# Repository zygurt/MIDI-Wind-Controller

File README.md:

# MIDI-Wind-Controller

## A brief overview of the repo

- 3D designs contains dxf and svg files.  Basic design was done in Fusion 360 and then exported.
- Datasheets contains datasheets. Woah.
- src contains source code for doppler and Arduino Leonardo implementations, as well as the board schematic.  Currently midi messages are sent over USB, and shows the midi note number in binary on the LED grid on the doppler board.

## Known issues
- Pressing the low C key (D9) causes the doppler to crash.  Reducing the length of the readButtons() switch case to 7 statements stops the crashing.  The error isn't present on the Arduino Leonardo.
- The octave keys give incorrect values for C#. Top 2 octaves are swapped. Again, this error does not occur for the Arduino Leonardo.

Updates are occasionally posted on [Instagram](https://www.instagram.com/zygurt/)

## Current prototype status:

## Legacy information
Videos about the initial prototype can be found on [Youtube](https://www.youtube.com/watch?v=xT4aQg9pAro&list=PLZOH4oUjroN9ol0y3P3p1gkSgcQwLBbCZ)

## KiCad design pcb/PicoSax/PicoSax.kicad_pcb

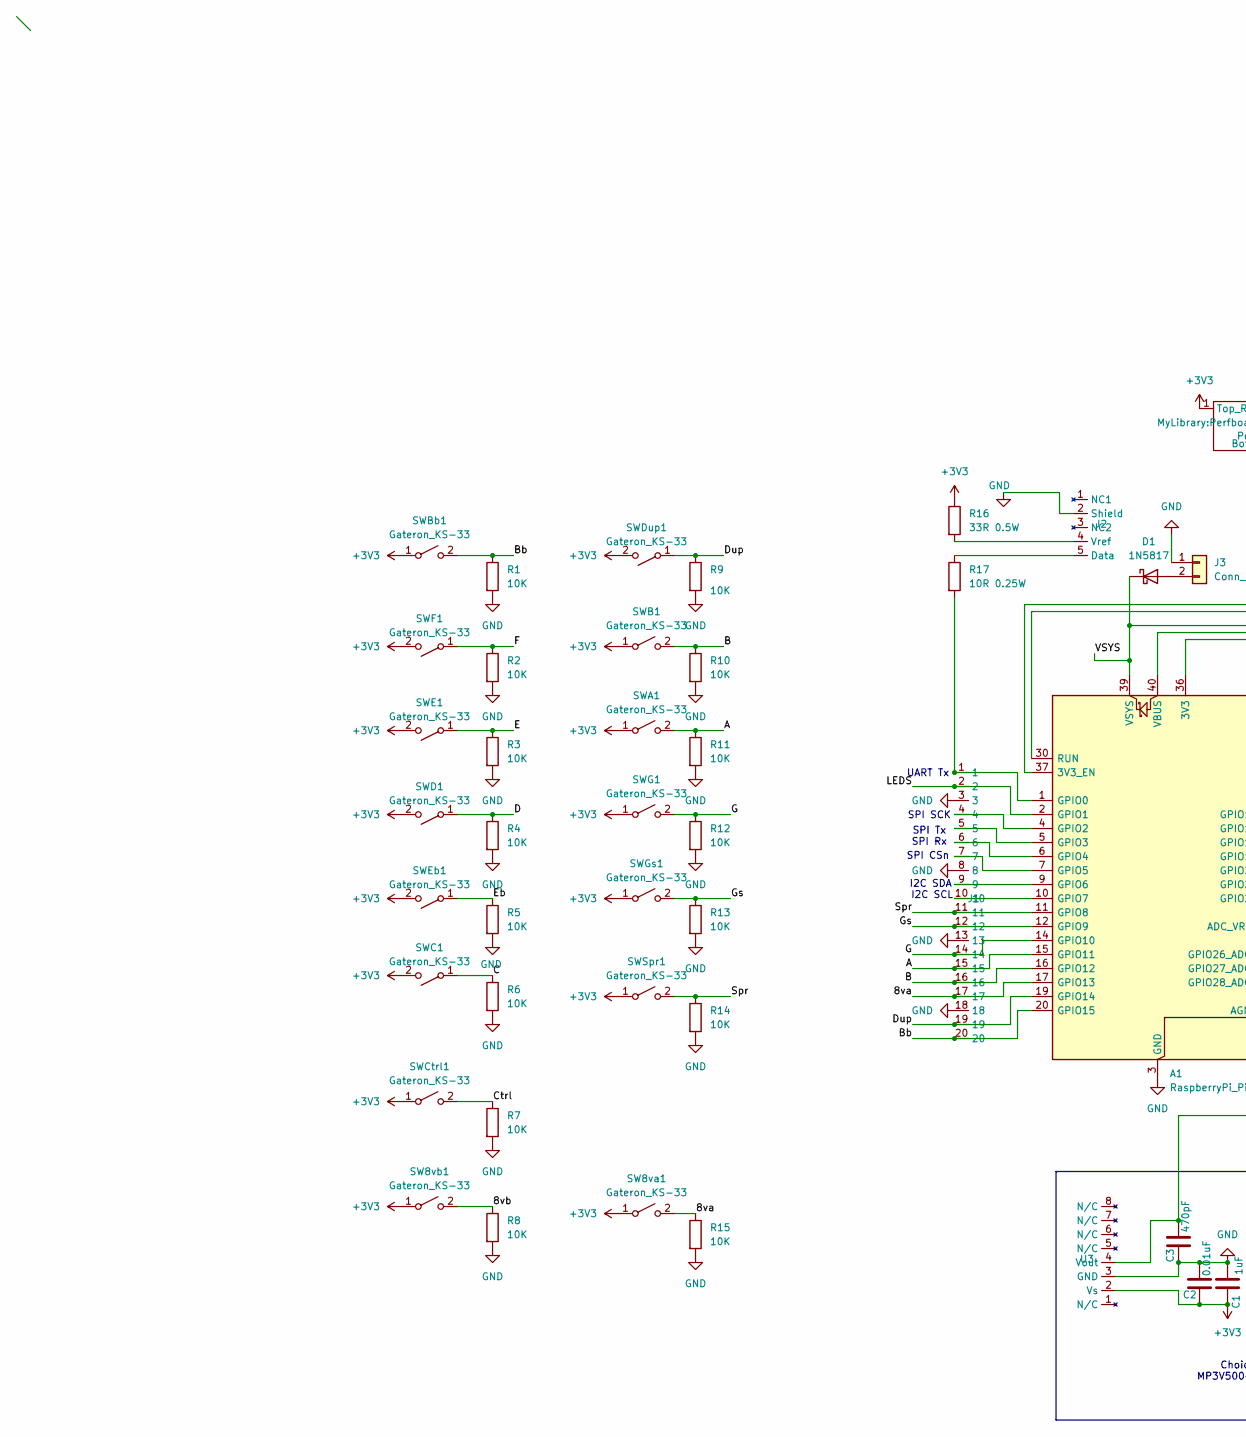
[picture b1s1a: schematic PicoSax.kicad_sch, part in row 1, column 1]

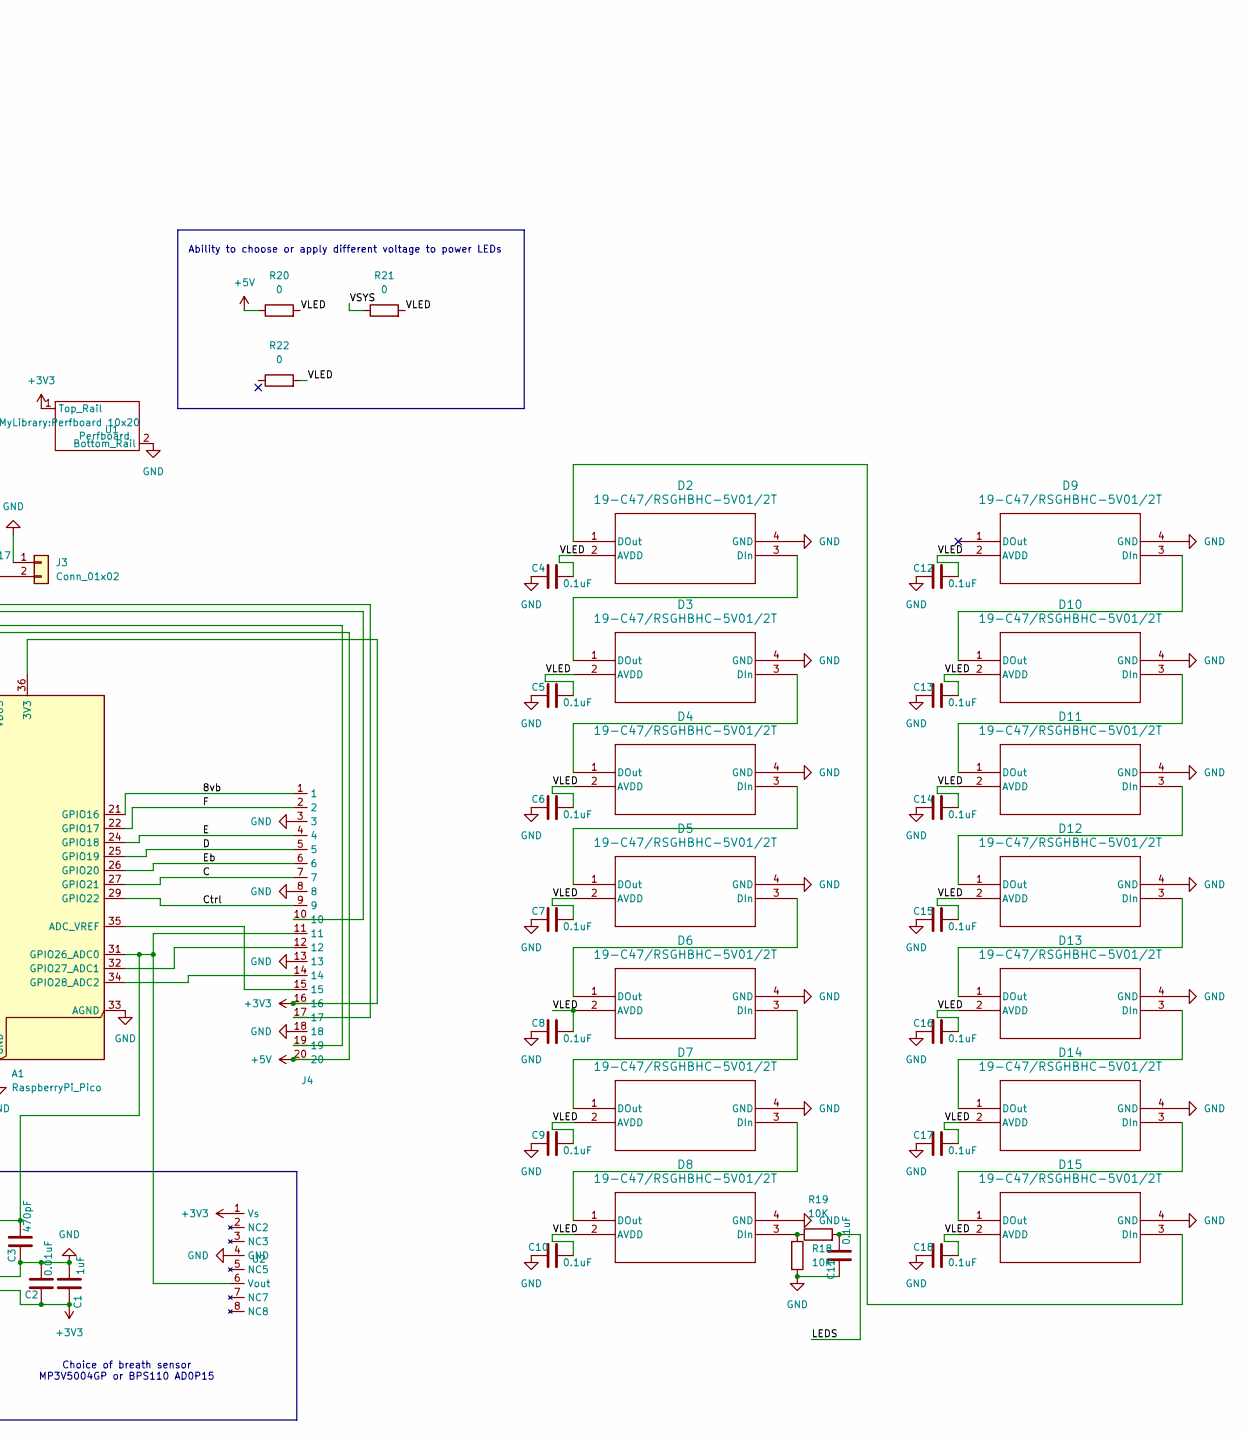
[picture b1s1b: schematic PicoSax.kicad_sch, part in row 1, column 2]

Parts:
A1: RaspberryPi_Pico; RaspberryPi_Pico_Common_Unspecified
C1: 1uF; C_0805_2012Metric_Pad1.18x1.45mm_HandSolder
C2: 0.01uF; C_0805_2012Metric_Pad1.18x1.45mm_HandSolder
C3: 470pF; C_0805_2012Metric_Pad1.18x1.45mm_HandSolder
C4, C5, C6, C7, C8, C9, C10, C11, C12, C13, C14, C15, C16, C17, C18: 0.1uF; C_0805_2012Metric_Pad1.18x1.45mm_HandSolder
D1: 1N5817; D_DO-41_SOD81_P10.16mm_Horizontal
D2, D3, D4, D5, D6, D7, D8, D9, D10, D11, D12, D13, D14, D15: 19-C47/RSGHBHC-5V01/2T; 19-C47_RSGHBHC-5V01-2T
J1, J4: PiPico Header
J2: MIDI_DIN5
J3: Conn_01x02; PinHeader_1x02_P2.54mm_Vertical
R1, R2, R3, R4, R5, R6, R7, R8, R9, R10, R11, R12, R13, R14, R15, R18, R19: 10K; R_0805_2012Metric_Pad1.20x1.40mm_HandSolder
R16: 33R 0.5W; R_1210_3225Metric_Pad1.30x2.65mm_HandSolder
R17: 10R 0.25W; R_0805_2012Metric_Pad1.20x1.40mm_HandSolder
R20, R21, R22: 0; R_0805_2012Metric_Pad1.20x1.40mm_HandSolder
SW8va1, SW8vb1: Gateron_KS-33; KS-33
SWA1: Gateron_KS-33; KS-33
SWB1: Gateron_KS-33; KS-33
SWBb1: Gateron_KS-33; KS-33
SWC1: Gateron_KS-33; KS-33
SWCtrl1: Gateron_KS-33; KS-33
SWD1: Gateron_KS-33; KS-33
SWDup1: Gateron_KS-33; KS-33
SWE1: Gateron_KS-33; KS-33
SWEb1: Gateron_KS-33; KS-33
SWF1: Gateron_KS-33; KS-33
SWG1: Gateron_KS-33; KS-33
SWGs1: Gateron_KS-33; KS-33
SWSpr1: Gateron_KS-33; KS-33
U1: Perfboard; Perfboard 10x20
U2: BPS110 AD0P15
U3: MP3V5004GP

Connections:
+3V3: A1.36 (3V3), C1.2, C2.2, J4.16, R16.1, SW8va1.1 (A), SW8vb1.1 (A), SWA1.1 (A), SWB1.1 (A), SWBb1.1 (A), SWC1.2 (B), SWCtrl1.1 (A), SWD1.2 (B), SWDup1.2 (B), SWE1.2 (B), SWEb1.2 (B), SWF1.2 (B), SWG1.1 (A), SWGs1.1 (A), SWSpr1.1 (A), U1.1 (Top_Rail), U2.1 (Vs), U3.2 (Vs)
+5V: A1.40 (VBUS), J4.20, R20.1
/8va: A1.17 (GPIO13), J1.17, R15.1, SW8va1.2 (B)
/8vb: A1.21 (GPIO16), J4.1, R8.1, SW8vb1.2 (B)
/A: A1.15 (GPIO11), J1.15, R11.1, SWA1.2 (B)
/B: A1.16 (GPIO12), J1.16, R10.1, SWB1.2 (B)
/Bb: A1.20 (GPIO15), J1.20, R1.1, SWBb1.2 (B)
/C: A1.27 (GPIO21), J4.7, R6.1, SWC1.1 (A)
/Ctrl: A1.29 (GPIO22), J4.9, R7.1, SWCtrl1.2 (B)
/D: A1.25 (GPIO19), J4.5, R4.1, SWD1.1 (A)
/Dup: A1.19 (GPIO14), J1.19, R9.1, SWDup1.1 (A)
/E: A1.24 (GPIO18), J4.4, R3.1, SWE1.1 (A)
/Eb: A1.26 (GPIO20), J4.6, R5.1, SWEb1.1 (A)
/F: A1.22 (GPIO17), J4.2, R2.1, SWF1.1 (A)
/G: A1.14 (GPIO10), J1.14, R12.1, SWG1.2 (B)
/Gs: A1.12 (GPIO9), J1.12, R13.1, SWGs1.2 (B)
/LEDS: A1.2 (GPIO1), C11.1, J1.2, R19.2
/Spr: A1.11 (GPIO8), J1.11, R14.1, SWSpr1.2 (B)
/VLED: C4.1, C5.1, C6.1, C7.1, C8.1, C9.1, C10.1, C12.1, C13.1, C14.1, C15.1, C16.1, C17.1, C18.1, D2.2 (AVDD), D3.2 (AVDD), D4.2 (AVDD), D5.2 (AVDD), D6.2 (AVDD), D7.2 (AVDD), D8.2 (AVDD), D9.2 (AVDD), D10.2 (AVDD), D11.2 (AVDD), D12.2 (AVDD), D13.2 (AVDD), D14.2 (AVDD), D15.2 (AVDD), R20.2, R21.2, R22.2
/VSYS: A1.39 (VSYS), D1.1 (K), J4.19, R21.1
GND: A1.3 (GND), A1.8 (GND), A1.13 (GND), A1.18 (GND), A1.23 (GND), A1.28 (GND), A1.33 (AGND), A1.38 (GND), C1.1, C2.1, C3.2, C4.2, C5.2, C6.2, C7.2, C8.2, C9.2, C10.2, C11.2, C12.2, C13.2, C14.2, C15.2, C16.2, C17.2, C18.2, D2.4 (GND), D3.4 (GND), D4.4 (GND), D5.4 (GND), D6.4 (GND), D7.4 (GND), D8.4 (GND), D9.4 (GND), D10.4 (GND), D11.4 (GND), D12.4 (GND), D13.4 (GND), D14.4 (GND), D15.4 (GND), J1.3, J1.8, J1.13, J1.18, J2.2 (Shield), J3.1, J4.3, J4.8, J4.13, J4.18, R1.2, R2.2, R3.2, R4.2, R5.2, R6.2, R7.2, R8.2, R9.2, R10.2, R11.2, R12.2, R13.2, R14.2, R15.2, R18.2, U1.2 (Bottom_Rail), U2.4 (GND), U3.3 (GND)
unnamed: A1.37 (3V3_EN), J4.17
unnamed: A1.35 (ADC_VREF), J4.15
unnamed: A1.1 (GPIO0), J1.1, R17.2
unnamed: A1.4 (GPIO2), J1.4
unnamed: A1.5 (GPIO3), J1.5
unnamed: A1.6 (GPIO4), J1.6
unnamed: A1.7 (GPIO5), J1.7
unnamed: A1.9 (GPIO6), J1.9
unnamed: A1.10 (GPIO7), J1.10
unnamed: A1.31 (GPIO26_ADC0), C3.1, J4.11, U2.6 (Vout), U3.4 (Vout)
unnamed: A1.32 (GPIO27_ADC1), J4.12
unnamed: A1.34 (GPIO28_ADC2), J4.14
unnamed: A1.30 (RUN), J4.10
unnamed: D1.2 (A), J3.2
unnamed: D2.3 (DIn), D3.1 (DOut)
unnamed: D3.3 (DIn), D4.1 (DOut)
unnamed: D4.3 (DIn), D5.1 (DOut)
unnamed: D5.3 (DIn), D6.1 (DOut)
unnamed: D6.3 (DIn), D7.1 (DOut)
unnamed: D7.3 (DIn), D8.1 (DOut)
unnamed: D8.3 (DIn), R18.1, R19.1
unnamed: D10.3 (DIn), D11.1 (DOut)
unnamed: D9.3 (DIn), D10.1 (DOut)
unnamed: D11.3 (DIn), D12.1 (DOut)
unnamed: D12.3 (DIn), D13.1 (DOut)
unnamed: D13.3 (DIn), D14.1 (DOut)
unnamed: D14.3 (DIn), D15.1 (DOut)
unnamed: D2.1 (DOut), D15.3 (DIn)
unnamed: J2.5 (Data), R17.1
unnamed: J2.4 (Vref), R16.2

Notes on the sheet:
I2C SCL
SPI SCK
SPI Rx
UART Tx
SPI Tx
Ability to choose or apply different voltage to power LEDs
Choice of breath sensor MP3V5004GP or BPS110 AD0P15
SPI CSn
I2C SDA

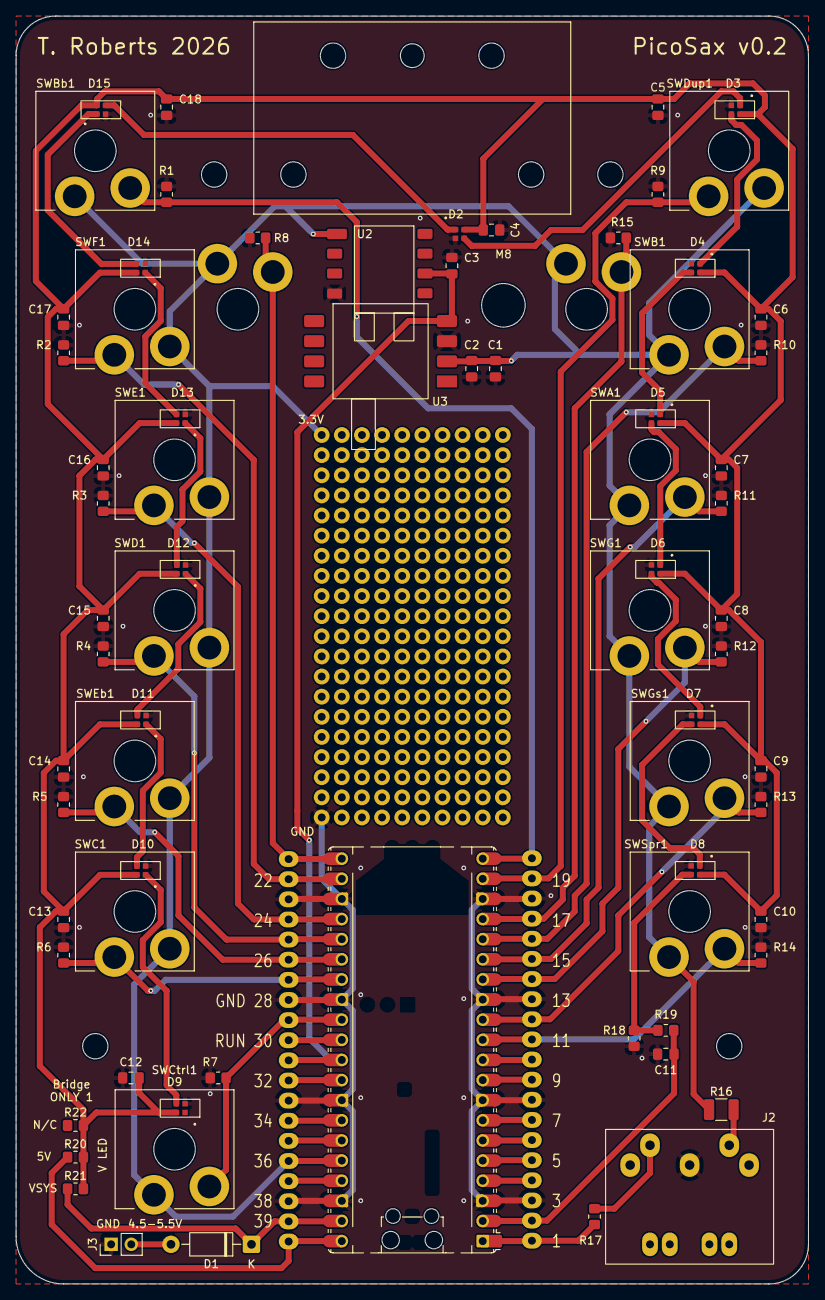
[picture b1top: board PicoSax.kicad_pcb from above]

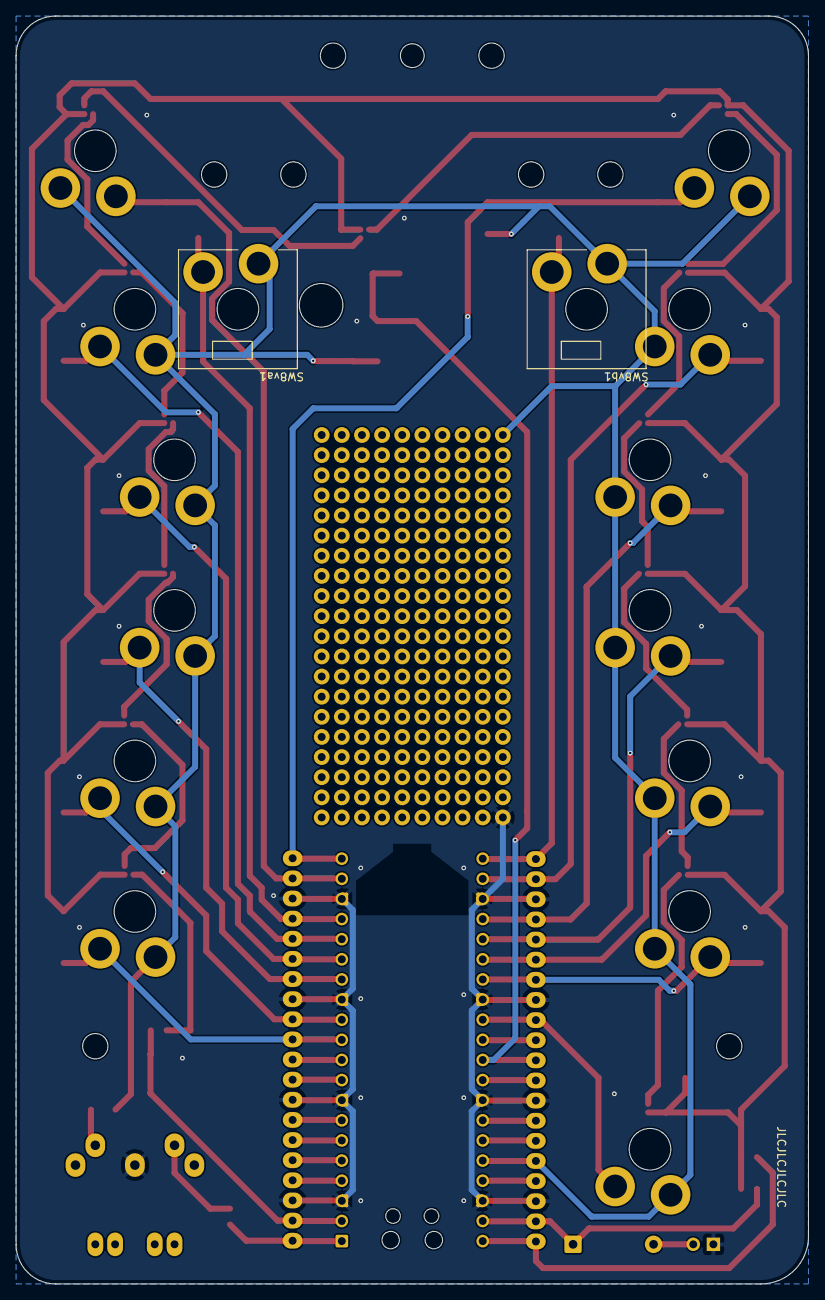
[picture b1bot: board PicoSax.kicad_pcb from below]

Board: 2 copper layers, 100.0 x 160.0 mm, 88 parts (2 on the bottom side), 51 nets.

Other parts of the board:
M1, M2, M3, M4, M5, M5#2, M6, M6#2: MountingHole_3.2mm_M3
M7: MountingHole_3mm
M8: MountingHole_5.5mm

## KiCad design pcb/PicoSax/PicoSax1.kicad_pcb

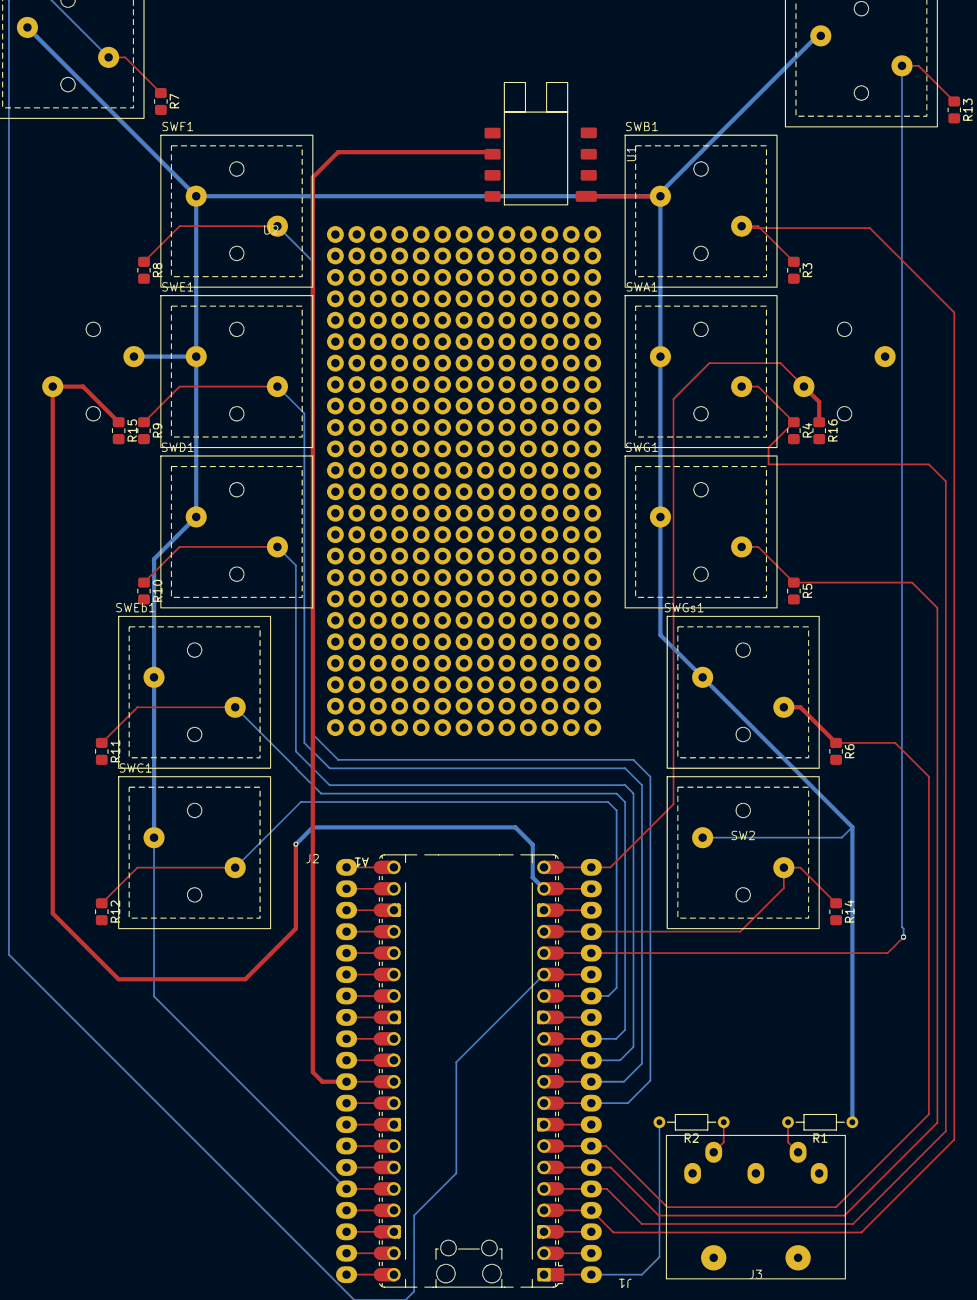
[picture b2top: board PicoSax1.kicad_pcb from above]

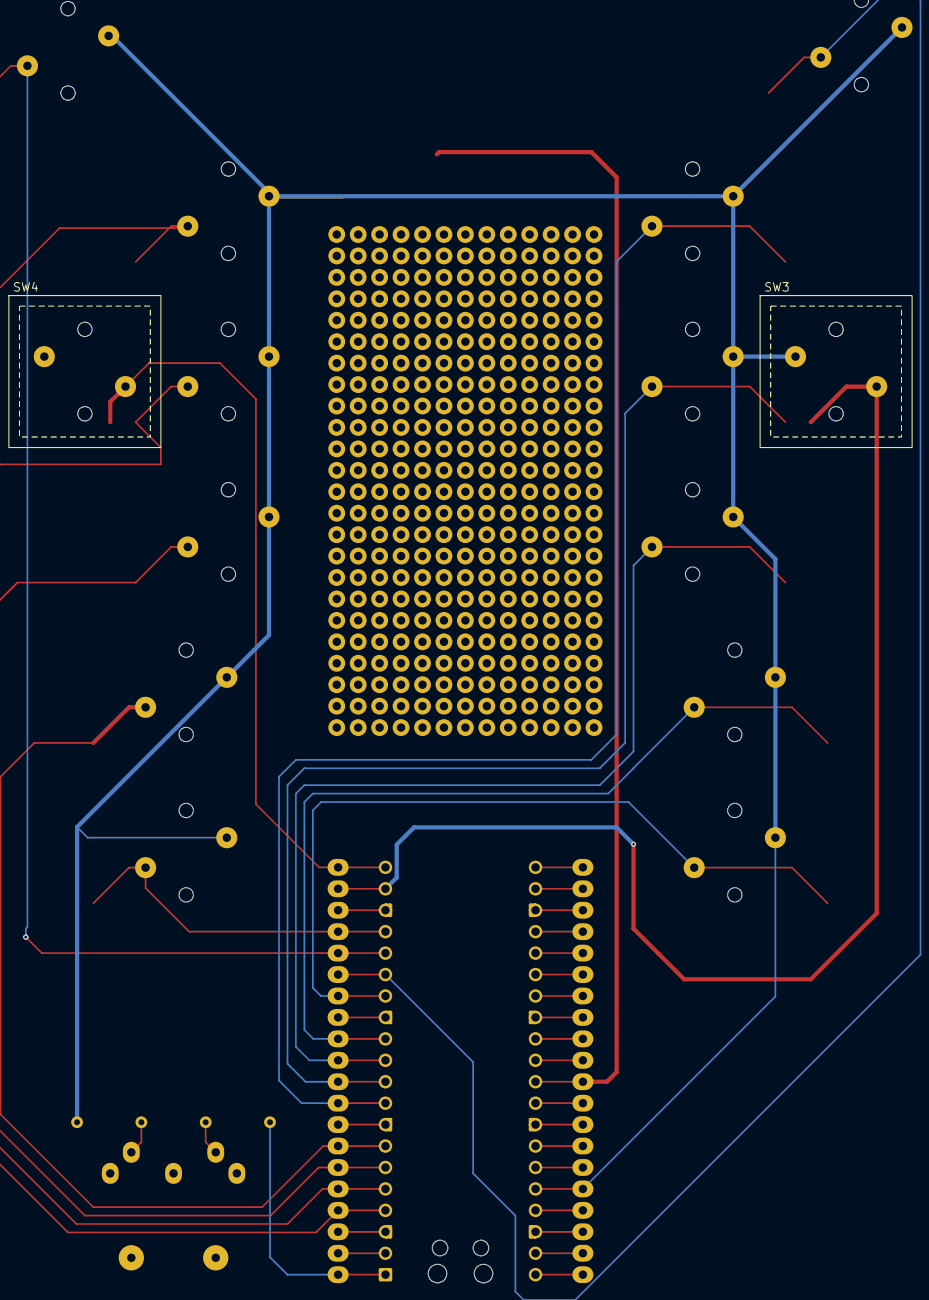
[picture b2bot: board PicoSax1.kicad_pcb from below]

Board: 2 copper layers, 36 parts (2 on the bottom side), 34 nets.

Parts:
A1: RaspberryPi_Pico; RaspberryPi_Pico_Common_Unspecified
J1, J2: PiPico Header
J3: MIDI_DIN5
R1: 33R 0.5W; R_Axial_DIN0204_L3.6mm_D1.6mm_P7.62mm_Horizontal
R2: 10R 0.25W; R_Axial_DIN0204_L3.6mm_D1.6mm_P7.62mm_Horizontal
R3, R4, R5, R6, R7, R8, R9, R10, R11, R12, R13, R14, R15, R16: 10K; R_0805_2012Metric_Pad1.20x1.40mm_HandSolder
SW1, SW2, SW3, SW4: Omron_B3K_L13L; Omron B3K L13L
SWA1: Omron_B3K_L13L; Omron B3K L13L
SWB1: Omron_B3K_L13L; Omron B3K L13L
SWBb1: Omron_B3K_L13L; Omron B3K L13L
SWC1: Omron_B3K_L13L; Omron B3K L13L
SWD1: Omron_B3K_L13L; Omron B3K L13L
SWE1: Omron_B3K_L13L; Omron B3K L13L
SWEb1: Omron_B3K_L13L; Omron B3K L13L
SWF1: Omron_B3K_L13L; Omron B3K L13L
SWG1: Omron_B3K_L13L; Omron B3K L13L
SWGs1: Omron_B3K_L13L; Omron B3K L13L
U1: BPS110 AD0P15
U2: Perfboard 13x24

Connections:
+3V3: A1.36 (3V3), J2.16, R1.1, SW1.1 (A), SW2.1 (A), SW3.1 (A), SW4.1 (A), SWA1.1 (A), SWB1.1 (A), SWBb1.1 (A), SWC1.1 (A), SWD1.1 (A), SWE1.1 (A), SWEb1.1 (A), SWF1.1 (A), SWG1.1 (A), SWGs1.1 (A), U1.1 (Vs)
GND: A1.3 (GND), A1.8 (GND), A1.13 (GND), A1.18 (GND), A1.23 (GND), A1.28 (GND), A1.33 (AGND), A1.38 (GND), J1.3, J1.8, J1.13, J1.18, J2.3, J2.8, J2.13, J2.18, J3.2 (Shield), R3.2, R4.2, R5.2, R6.2, R7.2, R8.2, R9.2, R10.2, R11.2, R12.2, R13.2, R14.2, R15.2, R16.2, U1.4 (GND)
unnamed: A1.37 (3V3_EN), J2.17
unnamed: A1.35 (ADC_VREF), J2.15
unnamed: A1.1 (GPIO0), J1.1, R2.2
unnamed: A1.4 (GPIO2), J1.4, R3.1, SWB1.2 (B)
unnamed: A1.5 (GPIO3), J1.5, R4.1, SWA1.2 (B)
unnamed: A1.6 (GPIO4), J1.6, R5.1, SWG1.2 (B)
unnamed: A1.7 (GPIO5), J1.7, R6.1, SWGs1.2 (B)
unnamed: A1.9 (GPIO6), J1.9, R8.1, SWF1.2 (B)
unnamed: A1.10 (GPIO7), J1.10, R9.1, SWE1.2 (B)
unnamed: A1.11 (GPIO8), J1.11, R10.1, SWD1.2 (B)
unnamed: A1.12 (GPIO9), J1.12, R11.1, SWEb1.2 (B)
unnamed: A1.14 (GPIO10), J1.14, R12.1, SWC1.2 (B)
unnamed: A1.15 (GPIO11), J1.15, R7.1, SWBb1.2 (B)
unnamed: A1.16 (GPIO12), J1.16, R13.1, SW1.2 (B)
unnamed: A1.17 (GPIO13), J1.17, R14.1, SW2.2 (B)
unnamed: A1.19 (GPIO14), J1.19, R15.1, SW3.2 (B)
unnamed: A1.20 (GPIO15), J1.20, R16.1, SW4.2 (B)
unnamed: A1.21 (GPIO16), J2.1
unnamed: A1.22 (GPIO17), J2.2
unnamed: A1.24 (GPIO18), J2.4
unnamed: A1.25 (GPIO19), J2.5
unnamed: A1.26 (GPIO20), J2.6
unnamed: A1.27 (GPIO21), J2.7
unnamed: A1.29 (GPIO22), J2.9
unnamed: A1.31 (GPIO26_ADC0), J2.11, U1.6 (Vout)
unnamed: A1.32 (GPIO27_ADC1), J2.12
unnamed: A1.34 (GPIO28_ADC2), J2.14
unnamed: A1.30 (RUN), J2.10
unnamed: A1.40 (VBUS), J2.20
unnamed: A1.39 (VSYS), J2.19
unnamed: J3.5 (Data), R2.1
unnamed: J3.4 (Vref), R1.2

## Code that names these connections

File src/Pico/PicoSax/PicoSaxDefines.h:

//Pin Assignment
// Pin	    Function	    Connection
// 1	    GPIO 0	        UART Tx
// 2	    GPIO 1	        LEDs
// 3	    GND	
// 4	    GPIO 2	        SPI SCK | UART 1 Tx
// 5	    GPIO 3	        SPI Tx | UART 1 Rx
// 6	    GPIO 4	        SPI Rx
// 7	    GPIO 5	        SPI CSn
// 8	    GND	
// 9	    GPIO 6	        I2C SDA
// 10	    GPIO 7	        I2C SCL
// 11	    GPIO 8	        Spr
// 12	    GPIO 9	        Gs
// 13	    GND	
// 14	    GPIO 10	        G
// 15	    GPIO 11	        A
// 16	    GPIO 12	        B
// 17	    GPIO 13	        8va
// 18	    GND	
// 19	    GPIO 14	        Dup
// 20	    GPIO 15	        Bb
// 21	    GPIO 16	        Bvb
// 22	    GPIO 17	        F
// 23	    GND	
// 24	    GPIO 18	        E
// 25	    GPIO 19	        D
// 26	    GPIO 20	        Eb
// 27	    GPIO 21	        C
// 28	    GND	
// 29	    GPIO 22	        Ctrl
// 30	    RUN	
// 31	    GPIO 26 | ADC0	Breath
// 32	    GPIO 27 | ADC1	
// 33	    AGND	
// 34	    GPIO 28 | ADC2	
// 35	    ADC_VREF	
// 36	    3V3	
// 37	    3V3 EN	
// 38	    GND	
// 39	    VSYS	
// 40	    VBUS	        5V (USB)

#define VERBOSE 0
#define BREATH_GPIO 26

#define breath_threshold 20 //Breath on/off threshold
#define breath_scale 0.5 //Breath scaling factor
#define breath_array_len 8
#define NEW_NOTE_TIMER 30000 //uS

#define CC_threshold 1
#define breath_CC 2

// UART defines
// By default the stdout UART is `uart0`, so we will use the second one
#define UART_ID uart0  //uart1
#define BAUD_RATE 31250// 31250 MIDI Baud // 115200 USB BAUD
#define DATA_BITS 8
#define STOP_BITS 1
#define PARITY UART_PARITY_NONE

// Use pins 4 and 5 for UART1
// Pins can be changed, see the GPIO function select table in the datasheet for information on GPIO assignments
#define UART_TX_PIN 0 //4
#define UART_RX_PIN 1 //5

// Global variables
float breath_at_rest = 0;
float breath_array[breath_array_len];
char prev_note = 0;
bool note_on = 0;
uint8_t breath_raw_midi = 0;
int prev_breath = 0;
uint8_t prev_CC = 0;
uint8_t current_CC = 0;
int8_t octave_transpose = 1;
int8_t octave_move = 0;
uint8_t semitone_transpose = 0;
bool menu = 0;

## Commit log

2022-02-22 ReadMe Update
2022-02-28 Added Schematic
2022-03-05 Change breath threshold
2022-03-13 bare-minimum
2022-03-13 Working on Leonardo
2022-03-24 Working Leonardo
2022-03-29 Update to Leonardo Version
2022-03-29 Readme
2022-03-29 Added image
2022-03-29 Schematic Update
2022-04-06 G# fingerings and Menu
2025-03-19 v3 PCB
    KiCAD PCB for v3
2025-03-19 KiCAD Backup
    Ready for production
2025-03-21 Tubing Hole and BOM
2025-03-24 Clean and Parts BOM
2025-03-25 PCB v0.11
2025-03-29 Pico Byte Values
2025-04-07 SVG and STEP
2025-04-10 datasheet
2025-05-06 LED code
2025-05-08 v0.2
    Updated LED footprint to have correct pin numbering. Redid layout and traces. Added helpful silkscreen for pi pico. Added some datasheets.
2025-05-08 v0.2 Silkscreen
2025-05-12 PicoSax SRC
2025-05-15 Compiles
2025-05-19 MIDI Implementation
2025-05-20 3D and USBuart
2025-05-24 Menu
2025-05-31 Working
    Notes are changing too fast, causing issues if more than one key changes state.
2025-08-14 move air pressure
2025-10-20 Mouthpiece mounting hole update
2025-10-22 Mouthpieces
2025-10-24 USB MIDI minor PCB tweaks
2025-10-27 Still Double triggering
2025-10-28 Cross Fingering fix-ish
    Reformatted code to be nested if statements to make it easier to read and manage each case, rather than using flags.
    Note debouncing now waits for the note to be steady for 30mS, rather than waiting every time there's a new note to check again. 30mS is borderline not long enough, but it would make fast grace notes 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
2025-10-29 MIDI Learn specific CC
    Also explored CC outputs on note change to confirm new note wait. Removed as they stopped other notes triggering.
    Occasionally a grace note or trill will be missed due to the wait.
2025-11-20 Fix Midi Note 0
    Also added another Bb fingering
    Added research into trills.
2025-11-25 Fixed midi note overflow
2026-01-14 KS-33 Update
    Routing still required. If wanting to work on previous version, see Backup.
2026-01-14 1N5817 datasheet
2026-01-15 Partial Route
2026-01-15 Routing Complete
    Still need to adjust locations of component references. And there is an issue in DRC about the footprints not matching. Not sure why that is as it wasn't a problem yesterday.
2026-03-24 V2 ready
